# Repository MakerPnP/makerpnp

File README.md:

<div align="center">

</div>

# MakerPnP

Cross-platform Pick-and-Place machine software, for Makers!

## Project Introduction

This project is work-in-progress, you can follow development using the links in the [links](#links) section below. 

## Project Status

Development is currently focused on the machine operations. Please see the dedicated repo here: https://github.com/MakerPnP/machine

In 2024/Q3 to 2025/Q2 development was focused on the workflow side of PCB assembly, UI selection and gerber files (types, parser, viewer).
Currently, a pure-rust desktop GUI for the planner is in a usable state, but un-polished.  Additionally, there are currently two functional cli tools,
planner_cli and variant builder and a stand-alone pure-rust gerber viewer.

## Planning

A PCB assembly job generally consists of the following things:

1) One or more PCBs that need populating, which may need populating on a single side or both sides or on rigid-flex layers.
2) A list of placements for each EDA design variant to be populated. 
3) A list of manufacturer + part codes for each part used in the job. (aka Bill-of-materials/BOM)
4) One or more processes.
4) A set of operations for each process.
5) A set of tasks for each operation.
6) One or more phases.
7) A set of parts for each phase.
8) One or more load-outs.
9) A defined placement ordering for each phase.

The processes are defined by the user, so that the planner works however components are attached: a pick-and-place
machine and reflow oven, placing and soldering by hand, applying glue and wave soldering, other machines or soldering
robots, or any mix of these. As with a PCB, each process is created in its own file, `<name>.process.json`, and then
added to a project, which keeps a copy of it until its processes are refreshed. A process can start from one of the
presets, `pnp` or `manual`, which match the examples below. Each task has a name chosen by the user, and a kind the
planner understands: generic, loading PCBs, or placing components. See
[`assets/specs/planner/core/02-processes.md`](assets/specs/planner/core/02-processes.md), and
[`assets/pcb-assembly.md`](assets/pcb-assembly.md) for the ways components are attached.

For example, a manual placement job for a double-sided 2x2 panel of PCBs with 2 designs, each design having 2 assembly
variants might be defined as follows:

```
Project
├── Processes
│   └── Process = Manual
│       └── Operations:
│           ├── 1
│           │   └── Tasks
│           │       └── Load PCBs
│           └── 2
│               └── Tasks
│                   ├── Place components
│                   └── Manually solder components
├── PCBs
|   └── 1 (Panel)
|       ├── Unit 1 (x=1, y=1) - Design A (Variant A) 
|       ├── Unit 2 (x=2, y=1) - Design A (Variant B)
|       ├── Unit 3 (x=1, y=2) - Design B (Variant A)
|       └── Unit 4 (x=2, y=2) - Design B (Variant B)
└── Phases
    ├── 1 - Top
    │   ├── Process = Manual    
    │   ├── Ordering: Panel Unit:Ascending, Part Cost:Ascending, Part Area:Ascending, Quantity:Desc
    │   └── Loadout: 'desk-top'.
    └── 2 - Bottom
        ├── Process = Manual
        ├── Ordering: Panel Unit:Ascending, Part Cost:Ascending, Part Area:Ascending, Quantity:Desc
        └── Loadout: 'desk-bottom'.
```

Similarly, the job for a single-sided 4x1 panel having a single design variant, using a mixed assembly
processes (SMT + TH) might be defined as follows:

```
Project
├── Processes
│   ├── Process = PnP
│   │   └── Operations:
│   │       ├── 1
│   │       │   └── Tasks
│   │       │       └── Load PCBs
│   │       ├── 2
│   │       │   └── Tasks
│   │       │       └── Place components
│   │       └── 3
│   │           └── Tasks
│   │               └── Reflow soldering
│   └── Process = Manual
│       └── Operations:
│           ├── 1
│           │   └── Tasks
│           │       └── Load PCBs
│           └── 2
│               └── Tasks
│                   ├── Place components
│                   └── Manually solder components
├── PCBs
|   └── 1 (Panel)
|       ├── Unit 1 (x=1, y=1) - Design A (Variant A) 
|       ├── Unit 2 (x=2, y=1) - Design A (Variant A)
|       ├── Unit 3 (x=3, y=1) - Design A (Variant A)
|       └── Unit 4 (x=4, y=1) - Design A (Variant A)
└── Phases
    ├── 1 - Top (Surface Mount / SMT)
    │   ├── Process = PnP
    │   ├── Ordering: Panel Unit:Ascending, Feeder Reference:Ascending, Part Cost:Ascending, Part Area:Ascending, Quantity:Ascending
    │   └── Loadout: 'pnp-machine-1'.
    └── 2 - Top (Through-hole / TH)
        ├── Process = Manual
        ├── Ordering: Panel Unit:Ascending, Part Cost:Ascending, Part Area:Ascending, Quantity:Desc
        └── Loadout: 'desk-top'.
```

## PlannerGUI

The planner GUI is used to define and manage the PCB assembly process, it works for automated, manual and mixed process
assembly jobs.

It's primary function is to allow you to define the assembly job and manage the job progress. It also generates artifacts
required for each process (e.g. a load-out and placement files).

Here's a recent screenshot:

## PlannerCLI

The PlannerCLI has the same functionality as the PlannerGUI, but with a command line interface.

Its `parts` mode uses the stores core (`planning/stores_app`), which has the user's data sources, for example
`planner_cli parts --source parts.csv list` lists a parts file's parts as CSV, and
`planner_cli parts --source parts.csv add --manufacturer RESCO --mpn RES1 --value LCSC=C1234` adds a part, as `set`
sets a part's other values and `remove` removes one. A change is refused if the file has changed since it was read, or
since the revision given with `--revision`. The stores core is pure: the CLI has the stores service
(`planning/stores_service`) read and write the file for it, as the GUI does. Its `table` mode shows another data
source's records as a table, for example `planner_cli table --kind bom --source board1_default_bom.csv list`
lists a variant's BOM as CSV, and `--kind eda-placements --eda-tool diptrace` a design's placements; the kinds are
`eda-placements`, `part-mappings`, `substitutions`, `assembly-rules`, `placements` and `bom`. Part mappings,
substitutions and assembly rules can be changed too, for example
`planner_cli table --kind substitutions --source substitutions.csv add --eda diptrace --pattern name=R0402 --value name=RES_0402`
adds a substitution, and `--kind assembly-rules ... add --ref-des R1 --manufacturer RESCO --mpn RES1` an assembly
rule; `set`, `remove` and `move` change one, and `add-columns --eda kicad` adds an EDA tool's columns.

Here's the current help output:

```
$ ./target/debug/planner_cli.exe --help
Usage: planner_cli [OPTIONS] <--project <PROJECT_NAME>> <COMMAND>

Commands:
  create                          Create a new job
  add-pcb                         Add a PCB
  assign-variant-to-unit          Assign a design variant to a PCB unit
  assign-process-to-parts         Assign a process to parts
  create-phase                    Create a phase
  assign-placements-to-phase      Assign placements to a phase
  assign-feeder-to-load-out-item  Assign feeder to load-out item
  set-placement-ordering          Set placement ordering for a phase
  generate-artifacts              Generate artifacts
  record-phase-operation          Record phase operation
  record-placements-operation     Record placements operation
  reset-operations                Reset operations
  help                            Print this message or the help of the given subcommand(s)

Options:
      --trace [<TRACE>]         Trace log file
      --path <PATH>             Path [default: .]
      --project <PROJECT_NAME>  Project name
  -v, --verbose...              Increase logging verbosity
  -q, --quiet...                Decrease logging verbosity
  -h, --help                    Print help
  -V, --version                 Print version
```

## VariantBuilderCLI

The variant builder CLI is used to take output files from EDA tools (e.g. DipTrace, KiCad, EasyEDAPro) and build
normalized placement files for the Planner.  Normalizing consists of these main tasks:

1) Cross-referencing EDA tool BOM information with your part inventory, using rules.
2) Substituting parts, using rules.
3) Selecting suitable parts from potential candidates, using load-out and rules. 
4) Normalizing units and co-ordinate systems.

It's common in small-volume manufacturing to have just a single PnP machine with feeder load-out that you don't want
to change.  The Variant Builder can prefer to use parts that are already in the machine so that you have to change
as few feeders as possible.  This is particularly useful for users of machines with drag-pin feeders, such as the
CharmHigh CHMT32VA/CHMT32VB/CHMT48VA/CHMT48VB machines, where the feeders are not individually replaceable.  The 
variant builder software is sensitive to the knowledge that changing feeders and machine-setup can be a very
time-consuming process. 

A variant is defined in a variant builder's file, `<design name>_<variant name>.variant.json`, which is created,
configured, a few options at a time, and built, each with its own command. In the planner's GUI, it's a design variant,
created with "New design variant".

```
$ ./target/debug/variantbuilder_cli.exe create --file job1_default.variant.json --eda kicad --placements job1-all-pos.csv
$ ./target/debug/variantbuilder_cli.exe configure --file job1_default.variant.json --parts parts.csv --part-mappings part-mappings.csv
$ ./target/debug/variantbuilder_cli.exe build --file job1_default.variant.json
```

`build` writes `job1_default_placements.csv` and `job1_default_bom.csv`, unless `--output` and `--output-bom` say
otherwise. Here's the current help output for `configure`:

```
$ ./target/debug/variantbuilder_cli.exe configure --help
Configure a variant builder, setting only the options given

Usage: variantbuilder_cli configure [OPTIONS] --file <FILE>

Options:
      --file <FILE>
          Variant builder file, <design name>_<variant name>.variant.json
      --eda <EDA>
          EDA tool [possible values: diptrace, kicad, easyeda]
      --load-out <SOURCE>
          Load-out source
      --placements <SOURCE>
          Placements source
      --parts <SOURCE>
          Parts source
      --part-mappings <SOURCE>
          Part-mappings source
  -v, --verbose...
          Increase logging verbosity
      --global-substitutions [<SOURCE>...]
          Global substitution sources, shared by designs, none to clear them
  -q, --quiet...
          Decrease logging verbosity
      --design-substitutions [<SOURCE>...]
          Design substitution sources, applied before the global ones, none to clear them
      --ref-des-exclusion-list [<REF_DES>...]
          List of reference designators to exclude (test-pads, fiducials, etc), none to clear it
      --ref-des-no-place-list [<REF_DES>...]
          List of reference designators not to place (do-not-fit, etc), none to clear it
      --assembly-rules <SOURCE>
          Assembly rules source
      --output <FILE>
          Output CSV file [default: <name>_placements.csv]
      --output-bom <FILE>
          Output BOM CSV file (Currently JLCPCB format only) [default: <name>_bom.csv]
      --ref-des-list [<REF_DES>...]
          List of reference designators for assembly variant (all if there are none), none to clear it
      --clear <OPTION>...
          Options to clear [possible values: eda, load-out, placements, parts, part-mappings, assembly-rules, output, output-bom]
  -h, --help
          Print help
```

## Gerber Viewer

There's a stand-alone gerber viewer, it can render gerber files generated with DipTrace 4.3, KiCad 8.0, and other tools.

Here's a screenshot:

### Supported gerber features

Full details of supported gerber features are in the gerber-viewer library crate, here:

https://github.com/MakerPnP/gerber-viewer#supported-gerber-features

### Feedback 

If you have gerber files and have rendering issues, please create an issue with screenshots and a gerber file.  If
you're able to create a gerber file with just the elements that have issues that would be preferred.

## Getting started

Currently, you have to build from source, but WAIT! it's EASY!

1) install rust (use [Rustup](https://www.rust-lang.org/tools/install))
2) clone the repo (use git via `git clone https://github.com/MakerPnP/makerpnp.git`, or [download a zip file from github](https://github.com/MakerPnP/makerpnp/archive/refs/heads/master.zip)) and extract it.
3) run the following commands in your terminal:
```
cd makerpnp
cargo build --release
```

After it's built there's executable files in the `target/release` directory:

```
$ ls -g target/release/*.exe
-rwxr-xr-x 2 None 13341184 Apr 28 14:06 target/release/gerber_viewer_egui.exe
-rwxr-xr-x 2 None  5775872 Apr 28 14:06 target/release/planner_cli.exe
-rwxr-xr-x 2 None 22119936 Apr 28 14:06 target/release/planner_gui_egui.exe
-rwxr-xr-x 2 None  3703296 Apr 28 14:06 target/release/variantbuilder_cli.exe
```

## Running the tools

The CLI tools can be run from anywhere, they are self-contained.
The GUI tools need to be run from the corresponding source directory as they require assets.  e.g.

```
cd planning/planner_gui_egui
../../target/release/planner_gui_egui.exe
```

## Architecture

The current architecture is to use Crux to provide rust-based back-ends (cores), and then to write Crux
'shells', also in rust, to provide front-ends (GUI/CLI) or APIs (e.g. web/rpc/etc) which use the common cores.  This
does add a layer of complexity, but should future-proof the project somewhat and also allows creation of non-rust
native apps that use the rust core.  Check out the 'Crux' documentation.

Given the state of Rust GUI frameworks, and that a 3 month-long investigation was done and documented in the form of a 
40+ livestream series. Using Crux gives the project a way of being able to change the GUI library for a different one
if the chosen GUI library, egui, does not meet future requirements.  This approach turned out to be very useful when
the Cushy GUI framework was replaced with egui.

See:
* Comparison of GUI libraries - https://docs.google.com/spreadsheets/d/1cxH_GgzrGDpXm4CN0cWvQ9RF_PLf6HEvVYcZhqOO0nc/edit?usp=sharing
* 'Trying Rust GUI tech in 2024' video series playlist - https://www.youtube.com/playlist?list=PLUCLWCDEWm8g7pHKQGE7Pokk4wiVU8rLl 

In the end, [egui](https://github.com/emilk/egui) was chosen for the GUI framework due to it's large community and
ability to create usable productivity-style GUIs.

Currently, it's thought that the software wil have these main components:
* Machine control - for co-ordination of hardware control through one or more drivers (gcode, cameras, vision).
* Machine operator UI - for machine configuration, job setup, and job operations.  feeders, cameras, head/nozzle/tool
  control, integrates with the machine control and planner components.  
* Planner UI - used to manage assembly projects, can be used without a pick-and-place machine, can generate artifacts
  usable by the operator UI (jobs), with EDA support (KiCad, Diptrace, EasyEda, etc.).

If you're familiar with 3D printing, you can think of the Planner as the 'slicer', the operator UI as the 3D printer's
front panel (touchscreen/buttons/display), and Machine control is a bit like the firmware, but not, since the machine
control component will interact with one or more drivers which will communicate to one or more pieces of hardware, each
with their own firmware, where as 3d printers usually only have one main control-board with a single piece of firmware. 

Examples of hardware which *could* be interacted with include:
* dedicated pink-and-place boards, usually via gcode (for x/y/z, vacuum, nozzle control, feeder actuators)
* 3d printer control boards, usually via gcode (again for x/y/z, vacuum, nozzle control, feeder actuators)
* feeder actuator systems (e.g. via RS485/RS232 + arbitrary protocol)
* conveyor/stacker systems (for loading pcbs into a machine)
* local or ip cameras
* and anything else you can dream of.

## Documentation

Written documentation for the project is sparse, further documentation will be created in due course.  However, the 
design and operation of the tools is detailed in the livestreams.

There are also functional tests which detail the expected input/output and operation sequences, so you can refer to
those to gain additional understanding.  See `planning/planner_cli/tests/planner.rs` and
`planning/variantbuilder_cli/tests/variantbuilder.rs`.

## Links

Please subscribe to be notified of live-stream events so you can follow the development process.

* Patreon: https://www.patreon.com/MakerPnP
* Source: https://github.com/MakerPnP
* Discord: https://discord.gg/ffwj5rKZuf
* YouTube: https://www.youtube.com/@MakerPnP
* X/Twitter: https://x.com/MakerPicknPlace

## Authors

* Dominic Clifton - Project founder and primary maintainer.

## License

TBD (Probably GPL3, Apache or MIT)

## Contributing

If you'd like to contribute, please raise an issue or a PR on the github issue tracker, work-in-progress PRs are fine
to let us know you're working on something, and/or visit the discord server.  See the  section above.

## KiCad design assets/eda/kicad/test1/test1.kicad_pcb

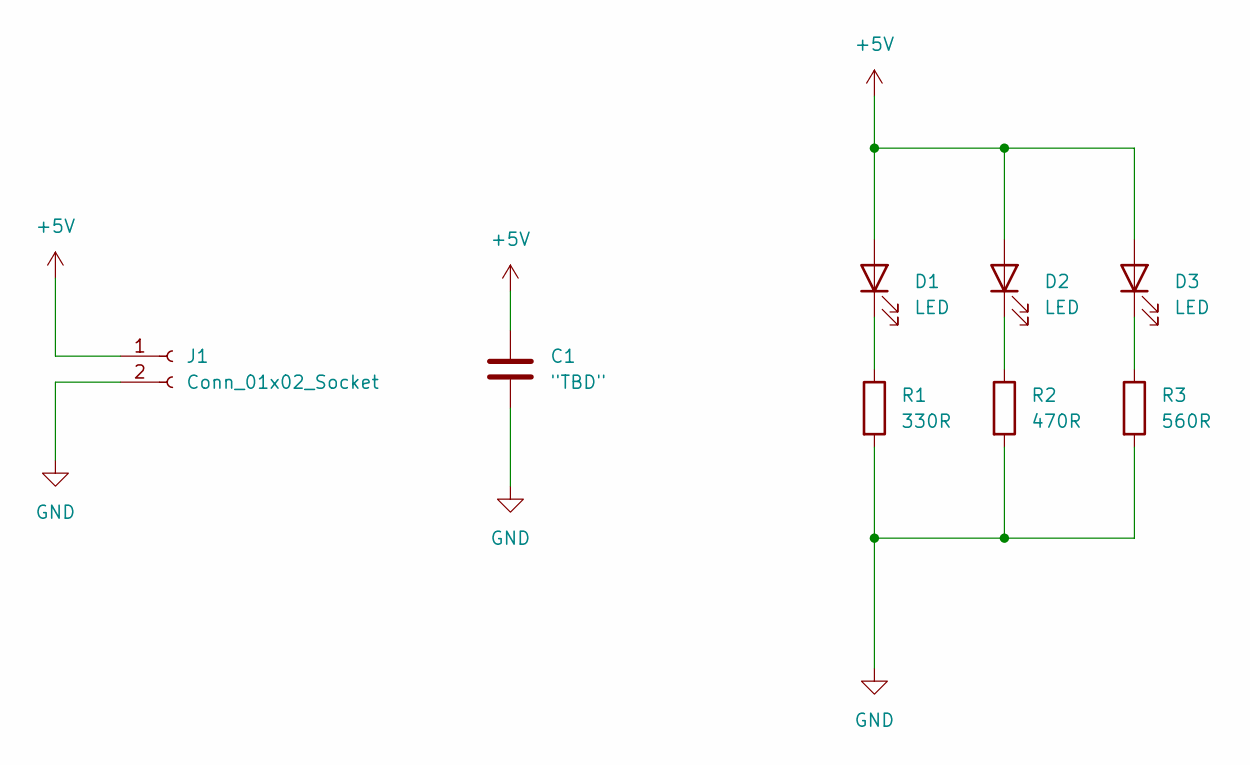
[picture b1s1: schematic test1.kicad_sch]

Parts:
C1: "TBD"; C_0402_1005Metric
D1, D2, D3: LED; LED_0603_1608Metric
J1: Conn_01x02_Socket; PinSocket_1x02_P2.54mm_Vertical
R1: 330R; R_0402_1005Metric
R2: 470R; R_0402_1005Metric
R3: 560R; R_0402_1005Metric

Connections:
+5V: C1.1, D1.2 (A), D2.2 (A), D3.2 (A), J1.1
GND: C1.2, J1.2, R1.2, R2.2, R3.2
unnamed: D1.1 (K), R1.1
unnamed: D2.1 (K), R2.1
unnamed: D3.1 (K), R3.1

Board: 2 copper layers, 8 parts (0 on the bottom side), 5 nets, no tracks yet.

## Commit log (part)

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2024-07-03 Example diptrace files
2024-07-03 Part Mapper: first cut of part mapping.
2024-07-03 Reorganize code into modules.
2024-07-04 PartMapping: fix compilation errors when building binaries.
2024-07-04 VariantBuilder: first cut of command line tool.
2024-07-04 VariantBuilder: read placements from CSV file
2024-07-04 VariantBuilder: delete unused code.
2024-07-05 VariantBuilder: Use the assembly variant processor to match the variant's placements. Minor naming improvements. Improve assembly variant processor error handling.
2024-07-05 VariantBuilder: Use clap attributes to provide version information.
2024-07-05 Readme: Use the github actions push event.
    * https://docs.github.com/en/actions/monitoring-and-troubleshooting-workflows/adding-a-workflow-status-badge#using-the-event-parameter
2024-07-08 VariantBuilder: Map EDA placements to Parts, using Part Mappings.
2024-07-08 VariantBuilder: Disable unused codepath.
2024-07-09 VariantBuilder: fix indentation (editor mishap)
2024-07-09 VariantBuilder: Delete some old commented out code.
2024-07-09 VariantBuilder: Allow alternative mappings.
2024-07-10 VariantBuilder: Improving the TODOs for KiCad support.
2024-07-11 VariantBuilder: Move the ordered assert macros into a mod.
2024-07-11 VariantBuilder: Display errors when the part mapper cannot resolve conflicts.
2024-07-11 VariantBuilder: Add error handling for the case where there are no mappings for a placement. Improved messaging around assembly variant matching.
2024-07-11 VariantBuilder: Renamed ProcessingResult to PlacementPartMappingResult.
2024-07-12 VariantBuilder: Add unit test for multiple matching mappings where one part is in the load-out.
2024-07-16 VariantBuilder: Support placement substitution chains.
2024-07-16 VariantBuilder: Write mapping results to CSV file.
2024-07-17 VariantBuilder: Support disabling placements by refdes.
    * Use for do-not-fit, no-place, test-points, fiducials, etc, but where you still want to be able to jog the camera/head/tool over the placement.
2024-07-18 VariantBuilder: Apply assembly rules before any other rule and stop further placement rule processing if one matches.
2024-07-20 Add KiCad example assets.
2024-07-20 VariantBuilder: Initial KiCad support.
2024-07-20 VariantBuilder: Improve naming in EdaSubstitutionRule to use 'transform' instead of 'change'.
2024-07-22 VariantBuilder: Refactor loading of Part Mappings from CSV by leveraging the serde 'flatten' attribute.
2024-07-22 VariantBuilder: Add a FIXME regarding a edge-case where an invalid substitution rule is specified.
2024-07-22 VariantBuilder: Use a default assembly variant if none is specified. Use all placements for an assembly variant if none are specified.
2024-07-22 VariantBuilder: Cleanup ordered assertions.
2024-07-22 VariantBuilder: Cleanup EDA module naming.
2024-07-22 JobBuilder: Create skeleton cli tool.
2024-07-29 Planner: Add command for assigning a pcb unit to the project.
2024-07-29 Planner: Assign parts to process.
2024-07-30 Planner: Create phase. Avoid serialization of empty lists.
2024-07-30 Planner: Refactored phases.
2024-07-30 Planner: Refactor process part assignments into part state.
    * In preparation for storing the assigned load-out for the part.
2024-07-31 Planner: Support multiple applicable processes for each part. Allow more flexible process naming. Delete assigning parts to a single load-out as it was wrong.
    * An error transcribing the design requirements to a diagram resulted in incorrect requirements being implemented.
    * Additionally it was found that 'Assign placements to phase' was missing from the requirements.
2024-07-31 Planner: Added support for PCB side when creating a phase
2024-08-01 Planner: Assign placements to phases.
2024-08-01 Planner: Added support for removing a placement between project refreshes.
2024-08-01 Planner: Make load-out mandatory when creating a phase.
2024-08-01 Planner: Show details when placement assignments are made.
2024-08-05 Planner: Update load-out when assigning placements to a phase. Ensure the load-out source is valid when creating a phase. Use builder pattern for load-out items. Use builder pattern and load-out sour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
2024-08-05 Planner: Assign feeders to load-out items. Rename 'name' argument to 'project'.
    * Currently unable to find a nice solution to say that the 'project' argument is only required when certain sub-commands are used without excessive code duplication of the project arguments. See all 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
    * Adding project_args to each project-specific sub command was tried (too much code duplication).
    * Defining two types of sub-commands was tried (very un-ergonomic).
    * Attempting to use 'group' on project-specific sub-commands was tried (failed).
    * Various other solutions were attempted, all of which failed or resulted in incorrect command/help/arguments/compilation-erro
2024-08-06 Planner: Set placement orderings.
2024-08-08 Placements: Added X,Y and Rotation. Added DipTrace specific rotation conversion. Assert placement updating messages. Provide defaults for EdaPlacements.
2024-08-09 Planner: Generate JSON project report document.
2024-08-09 Planner: Add phase operations to project report. Add PCBs to project.
    * Determining the operations requires PCBs to be added to the project first.
2024-08-10 Planner: Improve test robustness.
    * Ensure one phase has two placements that need placing that share the same part.
2024-08-12 Planner: Create issue when placement is not assigned to a phase.
2024-08-12 Planner: Refactor load-out operations.
2024-08-12 Planner: Relocate report generation code.
2024-08-12 VariantBuilder: Relocate EdaToolArg.
2024-08-12 Planner: Remove 'project_' prefix from some methods.
    * Redundant now that the methods are namespaced in a module.
2024-08-12 Planner: Replace UnitPath with ObjectPath. Improve robustness of ObjectPath.
2024-08-13 Planner: Improve process handling.
2024-08-13 VariantBuilder: Add support for default DipTrace 4.x CSV column headers.
2024-08-14 Part Mapping Store: workaround serde 'flatten' bug.
    * 'flatten' doesn't work if one of the fields contains only integers.
    * See https://github.com/BurntSushi/rust-csv/issues/344#issuecomment-2286126491
    Example CSV file that causes an issue is as follows:
    ```
    "Eda","Manufacturer","Mpn","Name","Value"
    "DipTrace","Molex","0479480001","0479480001",""
2024-08-14 Part Mapping Store: Skip serializing some eda specific fields if they are not set.
    * Using the 'eda' property to determine field inclusion, would be better. This will do for now though.
2024-08-14 Stores: Cleanup whitespace.
2024-08-14 Planner: Change record-placements-operation to use object paths instead of reference designators.
    * this is required so that a specific placement can be updated, instead of all placements that use the refdes; for a panel the same refdes is placed multiple times.
2024-08-14 Planner: De-duplicate issues. log all issues, after sorting them.
2024-08-14 Stores: Fix a second broken usage of serde flatten. Refactor and de-duplicate `build_eda_substitution` and `build_part_mapping` methods.
2024-08-15 Planner: Use the load-out source from the phase when assigning a feeder. Cleanup phase errors. Cleanup project name argument handling.
2024-08-15 Planner: Only save the project if it was modified when recording placements operation.
2024-08-15 Integration tests: Avoid warnings regarding unused macros.
2024-08-15 Planner: only report unit assignment updates if the value is different.
2024-08-15 Planner: Report when unit assignment is unchanged.
2024-08-15 VariantBuilder: Replaced EdaSubstitutionRuleCriteriaItem with ExactMatchCriterion.
2024-08-15 VariantBuilder: Fix criteria test module name.
2024-08-15 VariantBuilder: Add RegexMatchCriterion.
2024-08-15 VariantBuilder: Added support for regular expressions in substitutions.
2024-08-16 Planner: Improve placement orderings naming.
2024-08-16 Planner: Add phase ordering to the project. Update project report to list phases in the order they were created in. Added process to the phase overview in the report.
2024-08-16 Planner: Refactor display of phase orderings into a struct that implements Display
2024-08-16 Cli: Add support for reading arguments from files.
    e.g.
    test.args content:
    ```
    --help
    ```
    cli:
2024-08-16 Planner: Show names of files when generating artifacts. Generate phase artifacts in the order set by phase orderings.
2024-08-16 Cli: Don't require the '=' symbol.
    * this allows users to use the auto-complete functionality of the shell when building path names.
    * this required some argument pre-processing in the tests as each argument pair now needs to be split into an array before adding to the args array. (e.g. '--eda kicad' -> ['--eda', 'kicad']) where a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
2024-08-18 Planner: Remove completed FUTURE item regarding 'project' argument.
2024-08-19 Planner: Separate the process behavior from its name.
2024-08-19 Planner: Show phase operations overviews and operations in phases. Define phase operation kinds. Replace `Process::is_pnp()` with `Process::has_operation(ProcessOperationKind::AutomatedPnp)`. De-dupl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
2024-08-21 Planner: Fix indentation (editor mishap).
2024-08-21 Planner: Update phase operation status before generating artifacts. Update phase operation status when recording placement operations. Refactor phase operation status code.
    * Previously the phase operation status was transient and was used only for report generation.
2024-08-21 Planner: Change logging level of phases when generating report.
2024-08-22 Planner: Log an operation history when setting the loadpcbs operation to completed
2024-08-22 Planner: Fixed bug when recording placement operations where object path regular expressions that matched multiple placements only caused the first match to be updated.
2024-08-22 Planner: Support remaining operations when recording phase operations.
2024-08-22 Planner: Introduce a default state of 'Pending'. (aka 'Not-started').
    * for example placements cannot be incomplete or complete until placements are assigned to a phase.
2024-08-27 Convert planner to a crux app - WIP
2024-08-28 Port AssignVariantToUnit and add RefreshFromDesignVariants.
2024-08-28 Port AssignProcessToParts to app.
2024-08-28 Port AssignPlacementsToPhase to app.
2024-08-28 Port GenerateArtifacts to app.
2024-08-28 Rename planner to planner_cli.
2024-08-30 Failing to make a language selector dropdown
2024-08-30 Fix cargo warnings.
2024-08-30 Fix spacing
2024-08-30 Avoid the option now that a vec is used instead of the non-const `IndexMap::new()`
2024-09-03 WIP
    * no log output.
    * `use_router` panics.
2024-09-03 Move toolbar to its own file.
2024-09-03 WIP still trying to make sense of a) routing failures, b) multiple routers, c) what router the navigator tries to use.
2024-09-03 WIP
    * stack overflows when clicking Create
    * AlreadyBorrowedMut when clicking a document tab.
2024-09-03 Fix incorrect placement of a `Router` statement which was apparently wrong and caused stack overflows when clicking a document tab.
2024-09-12 Planner - Add navigation capability.
2024-09-12 PlannerGUI - Initial cut of GUI app using Vizia and Crux.
2024-09-12 PlannerGUI - Add language code code.
    * Untested due to crash from previous commit.
2024-09-13 PlannerGUI - Fixes to change language.
2024-09-13 PlannerGUI - Extract code from `main.rs` into their own module files.
2024-09-13 PlannerGUI - Relocate tabs.
2024-09-16 PlannerGUI - WIP
2024-09-16 PlannerGUI - FAIL - typing in popup causes window to be re-created.
2024-09-16 PlannerGUI - FAIL - even more failing
2024-09-16 PlannerGUI - Less failing!
2024-09-16 PlannerGUI - Cleanup signatures.
2024-09-16 PlannerApp - Fix warning.
2024-09-16 PlannerGUI - Fix warnings.
2024-09-16 PlannerGUI - Localize the window title of the New Project popup.
    * this required a fix to Vizia, see https://github.com/vizia/vizia/pull/508
2024-09-16 Planner - Distinguish between the project path and the project directory. Encode the project path when navigating.
2024-09-16 PlannerGUI - Add labels to the new project popup. Remove placeholders since they don't work well.
2024-09-16 PlannerGUI - Don't add a temporary tab now that it's possible to programmatically create a tab.
2024-09-17 PlannerGUI - Update project tree content.
2024-09-19 FAIL - attempt 2 at fixing the state.
2024-09-23 FAIL - result after talking with `@geom3trik`
    * The conclusion is the TabView is only fit for purpose for a static list of tabs and that there are no real-world uses where the tabs have changeable state in their content views which need to retai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
2024-09-23 PlannerApp - Add ViewRender capability. Different error handling to avoid 'Box<dyn Error>' on the model. Cleanup file/directory path naming. Update 'planner_cli' naming.
